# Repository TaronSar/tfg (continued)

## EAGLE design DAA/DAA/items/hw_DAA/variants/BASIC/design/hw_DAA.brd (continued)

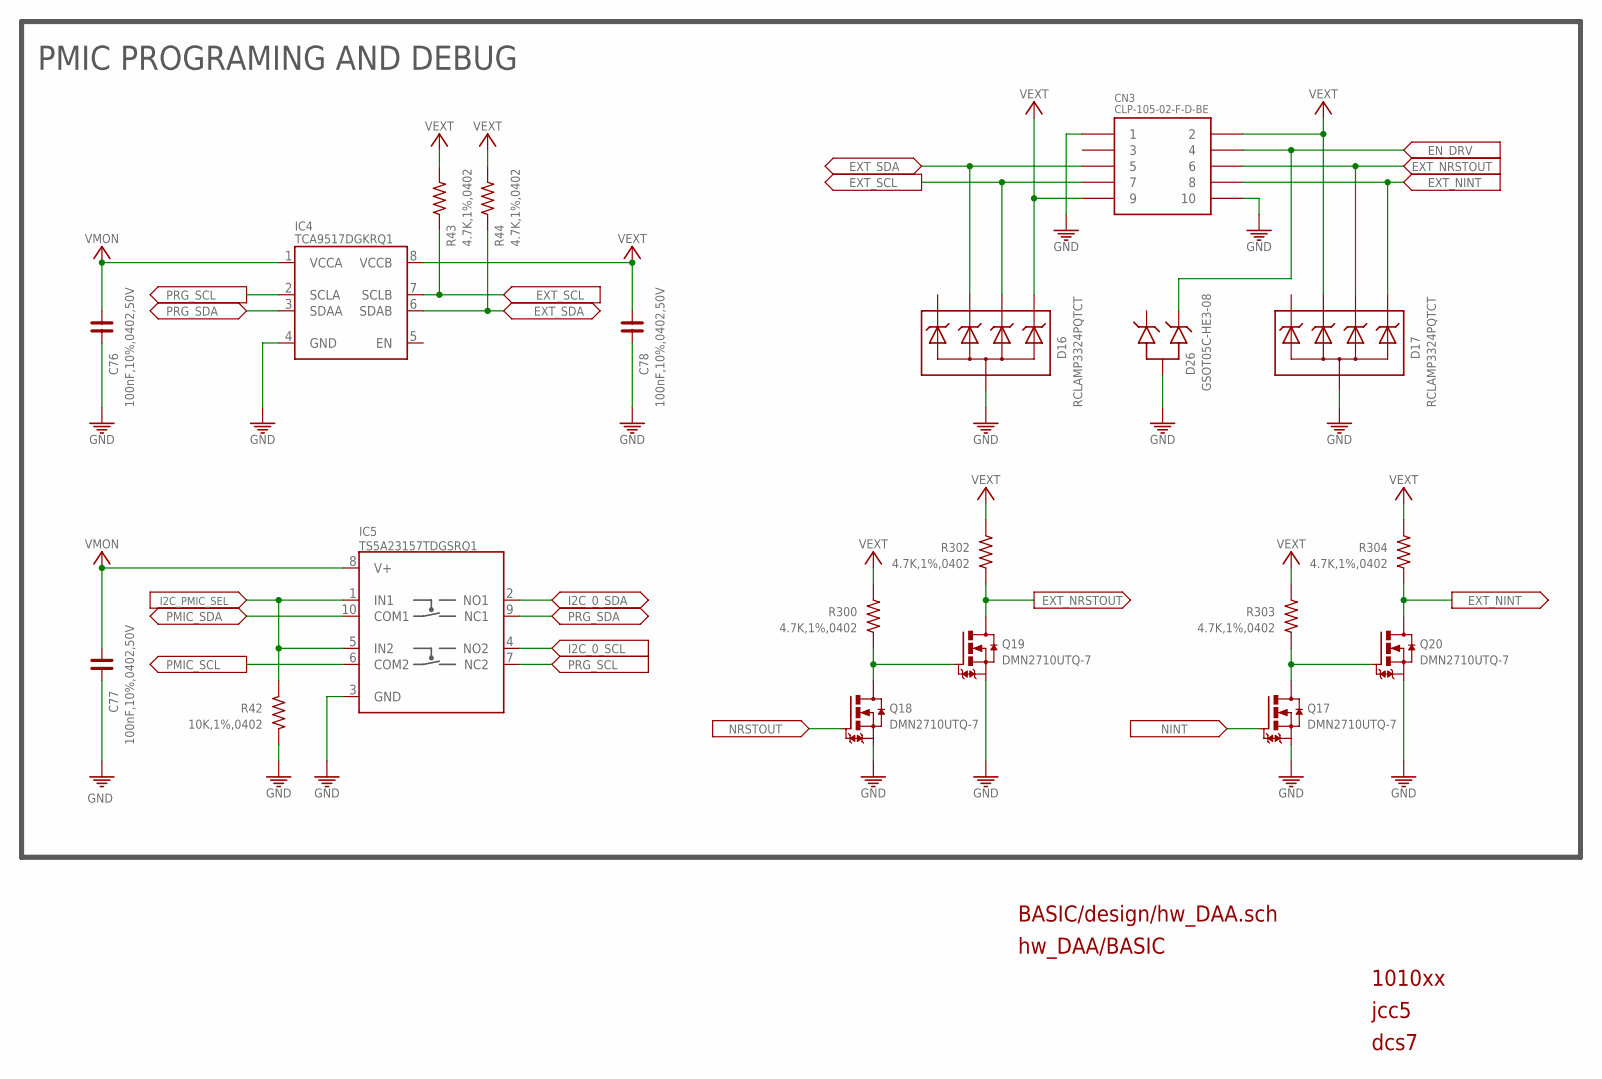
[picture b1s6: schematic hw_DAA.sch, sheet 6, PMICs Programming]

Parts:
C76, C77, C78: 100nF,10%,0402,50V; C0402
CN3: CLP-105-02-F-D-BE; CLP-105-02-X-D-BE
D16, D17: RCLAMP3324PQTCT; USON-10
D26: GSOT05C-HE3-08; SOT-23-3
IC4: TCA9517DGKRQ1; VSSOP-8(TEXAS)
IC5: TS5A23157TDGSRQ1; VSSOP-10
Q17, Q18, Q19, Q20: DMN2710UTQ-7; SOT-523
R42: 10K,1%,0402; R0402
R43, R44, R300, R302, R303, R304: 4.7K,1%,0402; R0402

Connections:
EN_DRV: CN3.4, D26.2; also elsewhere on the board
EXT_NINT: CN3.8, D17.5 (4), D17.6 (4), Q20.3 (D), R304.2
EXT_NRSTOUT: CN3.6, D17.4 (3), D17.7 (3), Q19.3 (D), R302.2
EXT_SCL: CN3.7, D16.4 (3), D16.7 (3), IC4.7 (SCLB), R43.2
EXT_SDA: CN3.5, D16.2, D16.9 (2), IC4.6 (SDAB), R44.2
GND: C76.2, C77.2, C78.2, CN3.1, CN3.10, D16.3 (5), D16.8 (5), D16.38 (5), D17.3 (5), D17.8 (5), D17.38 (5), D26.3, IC4.4 (GND), IC5.3 (GND), Q17.2 (S), Q18.2 (S), Q19.2 (S), Q20.2 (S), R42.1; also elsewhere on the board
I2C_0_SCL: IC5.4 (NO2); also elsewhere on the board
I2C_0_SDA: IC5.2 (NO1); also elsewhere on the board
I2C_PMIC_SEL: IC5.1 (IN1), IC5.5 (IN2), R42.2; also elsewhere on the board
unnamed: Q17.3 (D), Q20.1 (G), R303.2
unnamed: Q18.3 (D), Q19.1 (G), R300.2
NINT: Q17.1 (G); also elsewhere on the board
NRSTOUT: Q18.1 (G); also elsewhere on the board
PMIC_SCL: IC5.6 (COM2); also elsewhere on the board
PMIC_SDA: IC5.10 (COM1); also elsewhere on the board
PRG_SCL: IC4.2 (SCLA), IC5.7 (NC2)
PRG_SDA: IC4.3 (SDAA), IC5.9 (NC1)
VEXT: C78.1, CN3.2, CN3.9, D16.5 (4), D16.6 (4), D17.2, D17.9 (2), IC4.8 (VCCB), R43.1, R44.1, R300.1, R302.1, R303.1, R304.1
VMON: C76.1, C77.1, IC4.1 (VCCA), IC5.8 (V+); also elsewhere on the board

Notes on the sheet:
1010xx
jcc5
dcs7
PMIC PROGRAMING AND DEBUG
BASIC/design/hw_DAA.sch
hw_DAA/BASIC

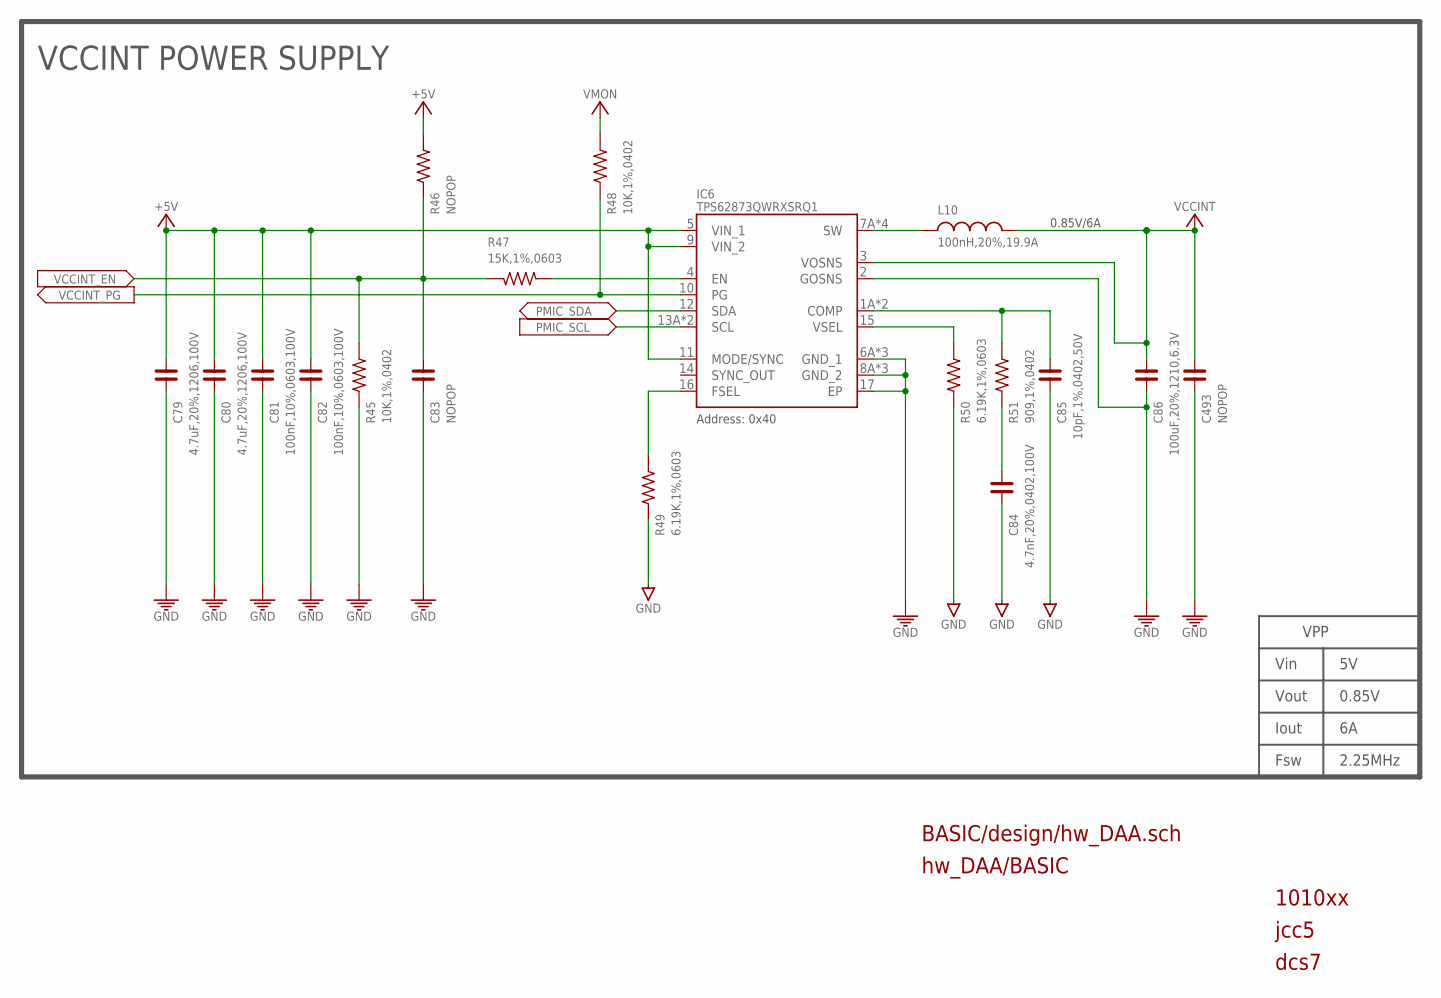
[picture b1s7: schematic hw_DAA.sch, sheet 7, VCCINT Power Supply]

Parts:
C79, C80: 4.7uF,20%,1206,100V; C1206
C81, C82: 100nF,10%,0603,100V; C0603
C83: NOPOP; C0402
C84: 4.7nF,20%,0402,100V; C0402
C85: 10pF,1%,0402,50V; C0402
C86: 100uF,20%,1210,6.3V; C1210
C493: NOPOP; C1210
IC6: TPS62873QWRXSRQ1; VQFN-16_RXS
L10: 100nH,20%,19.9A; XAL4020
R45, R48: 10K,1%,0402; R0402
R46: NOPOP; R0402
R47: 15K,1%,0603; R0603
R49, R50: 6.19K,1%,0603; R0603
R51: 909,1%,0402; R0402

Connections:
+5V: C79.1, C80.1, C81.1, C82.1, IC6.5 (VIN_1), IC6.9 (VIN_2), IC6.11 (MODE/SYNC), R46.2; also elsewhere on the board
GND: C79.2, C80.2, C81.2, C82.2, C83.2, C84.2, C85.2, C86.2, C493.2, IC6.2 (GOSNS), IC6.6A (GND_1), IC6.6B (GND_1), IC6.6C (GND_1), IC6.8A (GND_2), IC6.8B (GND_2), IC6.8C (GND_2), IC6.17 (EP), R45.1, R49.1, R50.1; also elsewhere on the board
unnamed: C85.1, IC6.1A (COMP), IC6.1B (COMP), R51.2
unnamed: C84.1, R51.1
unnamed: IC6.15 (VSEL), R50.2
unnamed: IC6.16 (FSEL), R49.2
unnamed: IC6.7A (SW), IC6.7B (SW), IC6.7C (SW), IC6.7D (SW), L10.1
unnamed: IC6.4 (EN), R47.2
PMIC_SCL: IC6.13A (SCL), IC6.13B (SCL); also elsewhere on the board
PMIC_SDA: IC6.12 (SDA); also elsewhere on the board
VCCINT: C86.1, C493.1, IC6.3 (VOSNS), L10.2; also elsewhere on the board
VCCINT_EN: C83.1, R45.2, R46.1, R47.1; also elsewhere on the board
VCCINT_PG: IC6.10 (PG), R48.1; also elsewhere on the board
VMON: R48.2; also elsewhere on the board

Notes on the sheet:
1010xx
jcc5
dcs7
0.85V/6A
Vout
Iout
Fsw
0.85V
Vin
VPP
2.25MHz
VCCINT POWER SUPPLY
Address: 0x40
BASIC/design/hw_DAA.sch
hw_DAA/BASIC

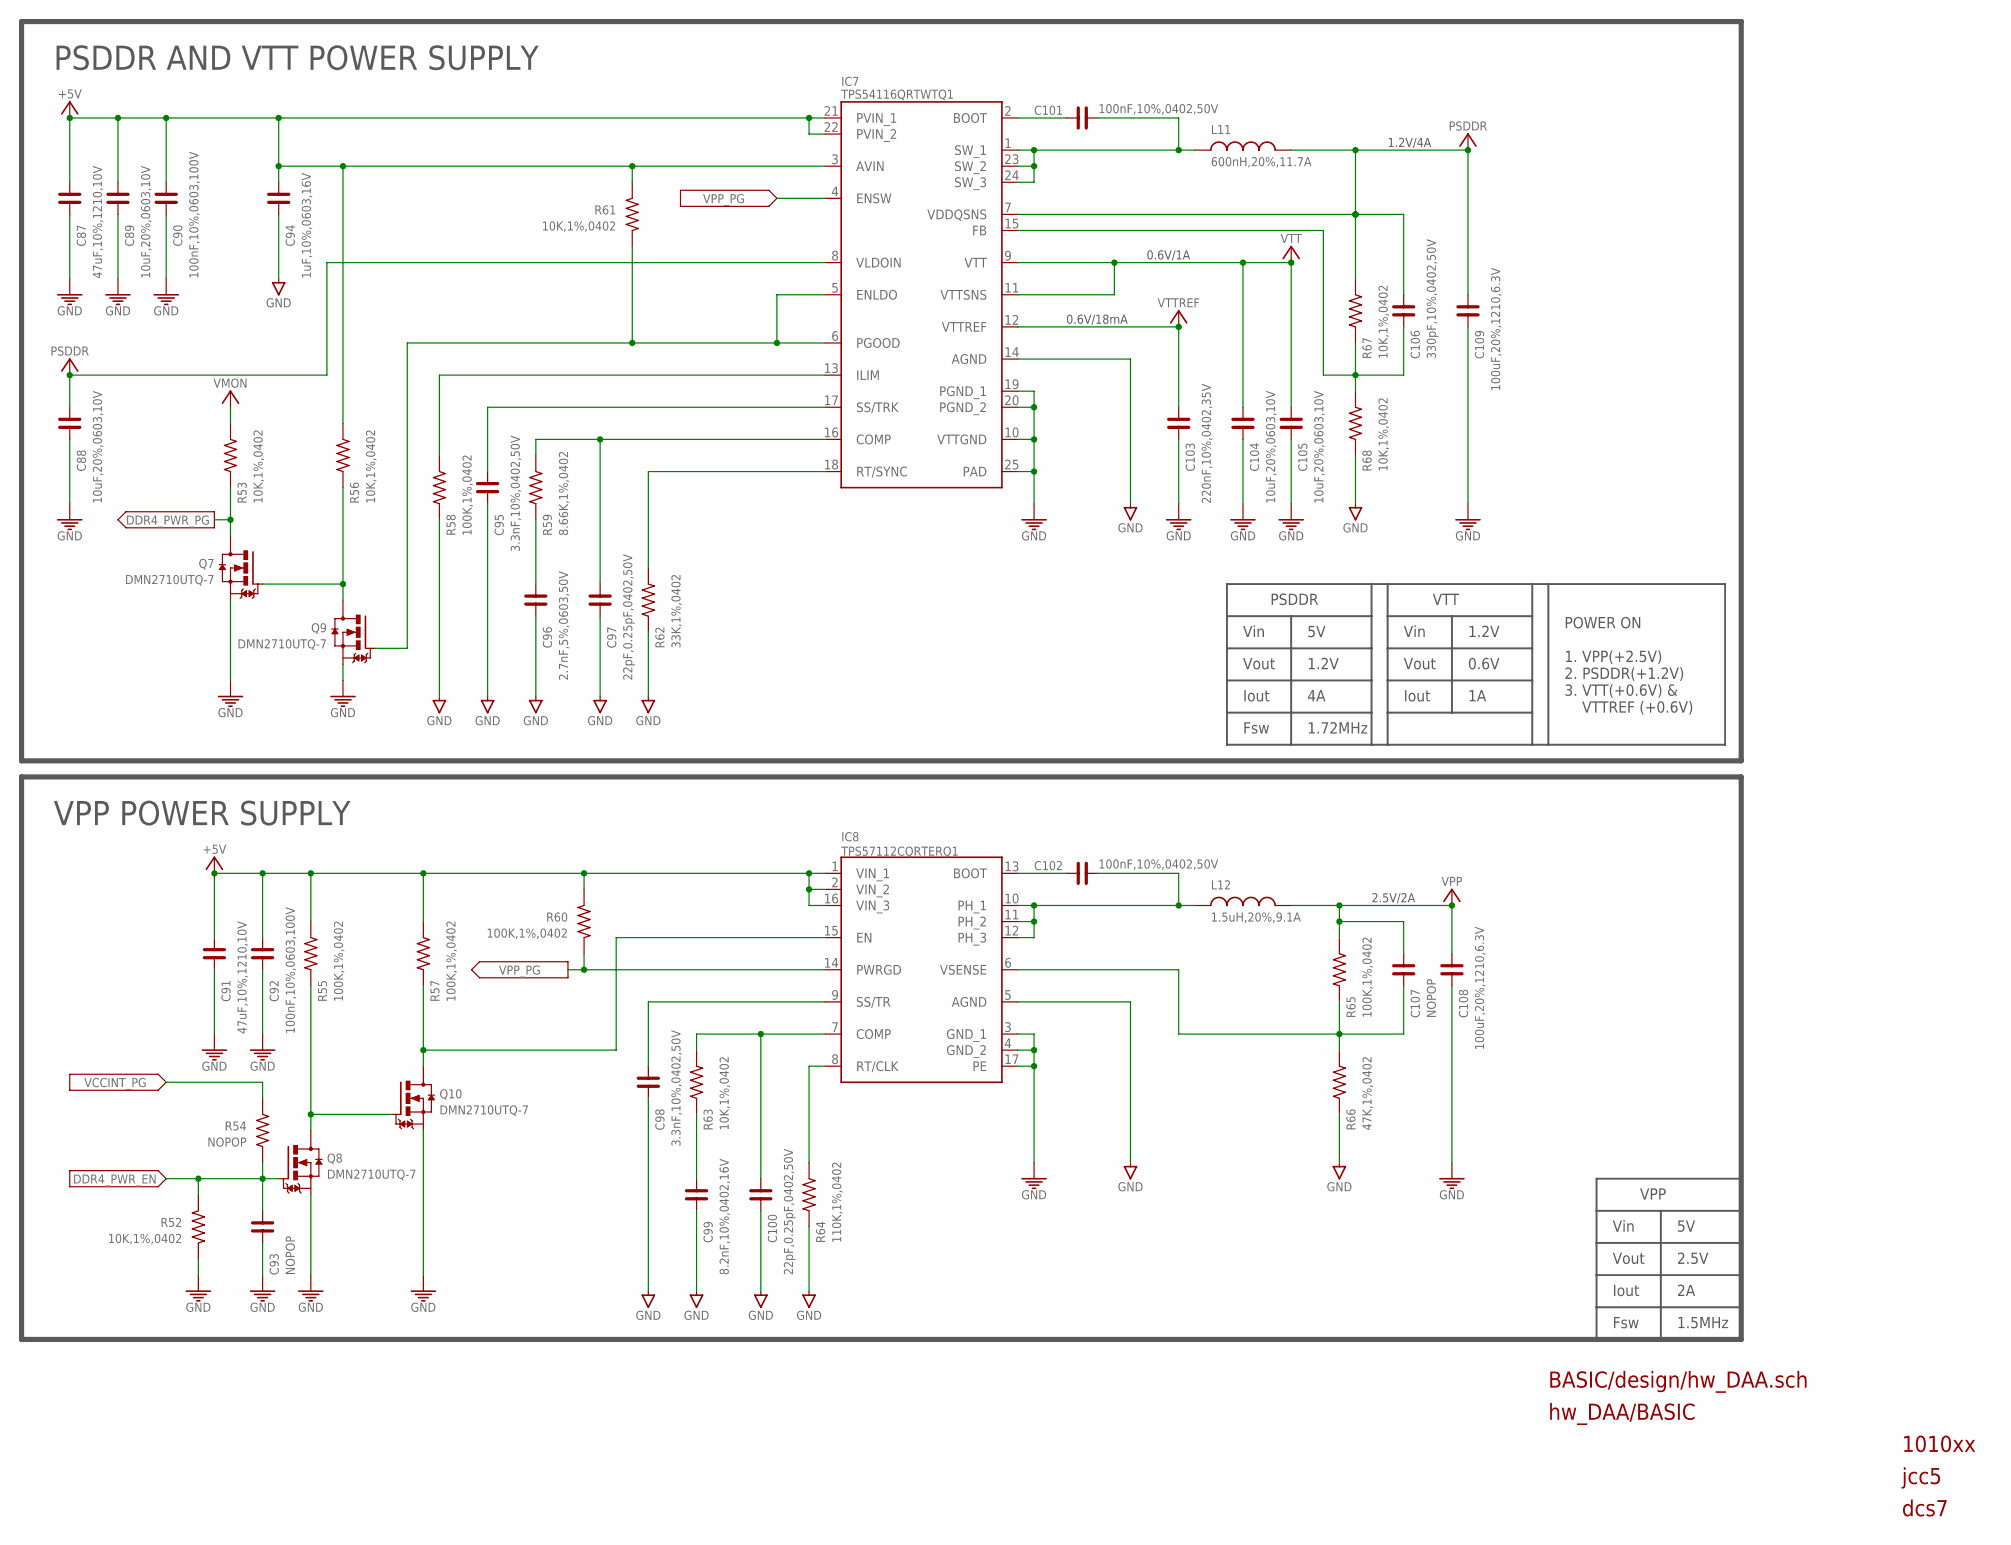
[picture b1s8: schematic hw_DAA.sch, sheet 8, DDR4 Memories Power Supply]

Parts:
C87, C91: 47uF,10%,1210,10V; C1210
C88, C89, C104, C105: 10uF,20%,0603,10V; C0603
C90, C92: 100nF,10%,0603,100V; C0603
C93, C107: NOPOP; C0402
C94: 1uF,10%,0603,16V; C0603
C95, C98: 3.3nF,10%,0402,50V; C0402
C96: 2.7nF,5%,0603,50V; C0603
C97, C100: 22pF,0.25pF,0402,50V; C0402
C99: 8.2nF,10%,0402,16V; C0402
C101, C102: 100nF,10%,0402,50V; C0402
C103: 220nF,10%,0402,35V; C0402
C106: 330pF,10%,0402,50V; C0402
C108, C109: 100uF,20%,1210,6.3V; C1210
IC7: TPS54116QRTWTQ1; WQFN-24
IC8: TPS57112CQRTERQ1; WQFN-16
L11: 600nH,20%,11.7A; XAL4020
L12: 1.5uH,20%,9.1A; XAL4020
Q7, Q8, Q9, Q10: DMN2710UTQ-7; SOT-523
R52, R53, R56, R61, R63, R67, R68: 10K,1%,0402; R0402
R54: NOPOP; R0402
R55, R57, R58, R60, R65: 100K,1%,0402; R0402
R59: 8.66K,1%,0402; R0402
R62: 33K,1%,0402; R0402
R64: 110K,1%,0402; R0402
R66: 47K,1%,0402; R0402

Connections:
+5V: C87.1, C89.1, C90.1, C91.1, C92.1, C94.1, IC7.3 (AVIN), IC7.21 (PVIN_1), IC7.22 (PVIN_2), IC8.1 (VIN_1), IC8.2 (VIN_2), IC8.16 (VIN_3), R55.2, R56.2, R57.2, R60.2, R61.2; also elsewhere on the board
DDR4_PWR_EN: C93.1, Q8.1 (G), R52.2, R54.1; also elsewhere on the board
DDR4_PWR_PG: Q7.3 (D), R53.1; also elsewhere on the board
EN_VPP: IC8.15 (EN), Q10.3 (D), R57.1
GND: C87.2, C88.2, C89.2, C90.2, C91.2, C92.2, C93.2, C94.2, C95.2, C96.2, C97.2, C98.2, C99.2, C100.2, C103.2, C104.2, C105.2, C108.2, C109.2, IC7.10 (VTTGND), IC7.14 (AGND), IC7.19 (PGND_1), IC7.20 (PGND_2), IC7.25 (PAD), IC8.3 (GND_1), IC8.4 (GND_2), IC8.5 (AGND), IC8.17 (PE), Q7.2 (S), Q8.2 (S), Q9.2 (S), Q10.2 (S), R52.1, R58.1, R62.1, R64.1, R66.1, R68.1; also elsewhere on the board
unnamed: C107.2, IC8.6 (VSENSE), R65.1, R66.2
unnamed: C98.1, IC8.9 (SS/TR)
unnamed: IC7.13 (ILIM), R58.2
unnamed: C95.1, IC7.17 (SS/TRK)
unnamed: C97.1, IC7.16 (COMP), R59.2
unnamed: C96.1, R59.1
unnamed: C100.1, IC8.7 (COMP), R63.2
unnamed: IC7.18 (RT/SYNC), R62.2
unnamed: C99.1, R63.1
unnamed: IC8.8 (RT/CLK), R64.2
unnamed: C106.2, IC7.15 (FB), R67.1, R68.2
unnamed: C102.2, IC8.13 (BOOT)
unnamed: C101.2, IC7.2 (BOOT)
unnamed: C101.1, IC7.1 (SW_1), IC7.23 (SW_2), IC7.24 (SW_3), L11.1
unnamed: C102.1, IC8.10 (PH_1), IC8.11 (PH_2), IC8.12 (PH_3), L12.1
unnamed: Q7.1 (G), Q9.3 (D), R56.1
unnamed: Q8.3 (D), Q10.1 (G), R55.1
PSDDR: C88.1, C106.1, C109.1, IC7.7 (VDDQSNS), IC7.8 (VLDOIN), L11.2, R67.2; also elsewhere on the board
PSDRR_PG: IC7.5 (ENLDO), IC7.6 (PGOOD), Q9.1 (G), R61.1
VCCINT_PG: R54.2; also elsewhere on the board
VMON: R53.2; also elsewhere on the board
VPP: C107.1, C108.1, L12.2, R65.2; also elsewhere on the board
VPP_PG: IC7.4 (ENSW), IC8.14 (PWRGD), R60.1
VTT: C104.1, C105.1, IC7.9 (VTT), IC7.11 (VTTSNS); also elsewhere on the board
VTTREF: C103.1, IC7.12 (VTTREF); also elsewhere on the board

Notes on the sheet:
1010xx
jcc5
dcs7
1.2V/4A
0.6V/1A
2.5V/2A
0.6V/18mA
PSDDR AND VTT POWER SUPPLY
VPP POWER SUPPLY
POWER ON 1. VPP(+2.5V) 2. PSDDR(+1.2V) 3. VTT(+0.6V) & VTTREF (+0.6V)
Vout
Iout
Fsw
1.2V
Vin
PSDDR
0.6V
VTT
1.72MHz
2.5V
VPP
1.5MHz
BASIC/design/hw_DAA.sch
hw_DAA/BASIC

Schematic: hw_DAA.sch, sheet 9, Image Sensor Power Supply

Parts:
C110, C111, C112: 10uF,10%,1206,35V; C1206
C113, C114, C119, C120, C121, C122: 10uF,10%,0805,16V; C0805
C115: 1uF,10%,0402,25V; C0402
C116, C118: 2.2uF,10%,0603,16V; C0603
C117: 100nF,10%,0402,50V; C0402
IC9: TPS65033000RGERQ1; VQFN-24
L13: 1.5uH,20%,2.3A; L201610
L14, L15: 1uH,20%,3.1A; L201610
R71, R73, R75: NOPOP; R0402
R72, R74: 0,5%,0402; R0402
R76: 1K,1%,0402; R0402

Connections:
!IMX_INT: IC9.22 (!INT), R72.1, R73.1
!IMX_RSTOUT: IC9.3 (!RSTOUT), R75.1; also elsewhere on the board
!TPS_INT: R72.2; also elsewhere on the board
+2V8: C118.1, IC9.24 (VLDO)
AVDD: C122.1, IC9.6 (FB_B1), L13.2; also elsewhere on the board
CM_SCL: IC9.1 (SCL); also elsewhere on the board
CM_SDA: IC9.2 (SDA); also elsewhere on the board
DVDD: C119.1, IC9.14 (FB_B3), L15.2; also elsewhere on the board
GND: C110.2, C111.2, C112.2, C113.2, C114.2, C115.2, C116.2, C118.2, C119.2, C120.2, C121.2, C122.2, IC9.5 (AGND), IC9.25 (PE), IC9.A11 (GND_1), IC9.A12 (GND_1), IC9.A21 (GND_2), IC9.A22 (GND_2), IC9.A31 (GND_3), IC9.A32 (GND_3), IC9.A41 (GND_4), IC9.A42 (GND_4); also elsewhere on the board
IMX_GPIO: IC9.19 (GPIO), R74.1
IMX_SEQ: IC9.10 (SEQ), R71.1, R76.2
IMX_VREG: C121.1, IC9.13 (VREG), R76.1
unnamed: IC9.20 (LX_B2), L14.1
unnamed: IC9.16 (LX_B3), L15.1
unnamed: C117.2, IC9.12 (BOOT)
unnamed: C117.1, IC9.11 (LX_B1), L13.1
unnamed: C114.1, IC9.4 (V1P8_INT)
OVDD: C115.1, C120.1, IC9.17 (VIO), IC9.18 (FB_B2), L14.2; also elsewhere on the board
POC: C110.1, C111.1, C112.1, C113.1, C116.1, IC9.7 (VSYS_S), IC9.8 (VSYS), IC9.9 (PVIN_B1), IC9.15 (PVIN_B3), IC9.21 (PVIN_B2), IC9.23 (PVINLDO); also elsewhere on the board
SER_GPIO0: R73.2; also elsewhere on the board
SER_PDB: R75.2; also elsewhere on the board
TPS_GPIO: R74.2; also elsewhere on the board
TPS_SEQ: R71.2; also elsewhere on the board

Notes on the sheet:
1010xx
jcc5
dcs7
3.3V/1.5A
1.8V/1.2A
1.2V/1.2A
IMAGE SENSOR POWER SUPPLY
1.8V
Address: 0x60
POWER ON 1. AVDD(+3.3V) 2. OVDD(+1.8V) 3. DVDD(+1.2V)
Vout
Iout
Fsw
3.3V
1.5A
2.3MHz
Vin
AVDD
1.2A
OVDD
1.2V
DVDD
BASIC/design/hw_DAA.sch
hw_DAA/BASIC

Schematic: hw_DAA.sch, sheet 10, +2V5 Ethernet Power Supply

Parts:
C123, C126: 2.2uF,10%,0603,16V; C0603
C124, C125: NOPOP; C0402
IC10: TPS74525PQWDRBRQ1; VSON-8
R77, R80, R81: NOPOP; R0402
R78, R79: 10K,1%,0402; R0402

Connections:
+2V5: C125.1, C126.1, IC10.1 (OUT), R80.2; also elsewhere on the board
+2V5_EN: C124.1, IC10.5 (EN), R77.1, R78.2; also elsewhere on the board
+2V5_PG: IC10.6 (PG), R79.1; also elsewhere on the board
+3V3: C123.1, IC10.8 (IN); also elsewhere on the board
DDR4_PWR_PG: R77.2; also elsewhere on the board
GND: C123.2, C124.2, C126.2, IC10.4 (GND), IC10.9 (EP), R78.1, R81.1; also elsewhere on the board
unnamed: C125.2, IC10.3 (NC_2/FB), R80.1, R81.2
VMON: R79.2; also elsewhere on the board

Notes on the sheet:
1010xx
jcc5
dcs7
+2V5 ETHERNET POWER SUPPLY
BASIC/design/hw_DAA.sch
hw_DAA/BASIC

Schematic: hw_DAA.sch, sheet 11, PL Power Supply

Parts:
C127, C140, C152, C155, C156, C158, C159: 47uF,20%,0603,4V; C0603
C128, C141, C142, C143, C145, C146, C147, C148, C151, C153, C154, C157: 10uF,20%,0402,4V; C0402
C129, C160: 330uF,20%,1210,2.5V; C1210
C130, C131, C132, C133, C136: 100uF,20%,0805,4V; C0805
C134: 470nF,10%,0402,16V; C0402
C135, C138, C139, C144, C149, C150: 4.7uF,20%,0402,10V; C0402
C137: 100nF,10%,0402,50V; C0402
FB4: BLM15PX121SH1D; L0402
IC11: XCZU15EG-2FFVB1156I; FFVB1156_NSMD
R82, R83: 100,1%,0402; R0402
R84, R85, R86, R87: 1K,1%,0402; R0402

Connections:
GND: C127.1, C128.1, C129.1, C130.1, C131.1, C132.1, C133.1, C135.1, C136.1, C138.1, C139.1, C140.1, C141.1, C142.1, C143.1, C144.1, C145.1, C146.1, C147.1, C148.1, C149.1, C150.1, C151.1, C152.1, C153.1, C154.1, C155.1, C156.1, C157.1, C158.1, C159.1, C160.1, R84.2, R85.2, R86.2, R87.2; also elsewhere on the board
GNDA: C134.1, C137.1; also elsewhere on the board
MGTAVCC: C135.2, C149.2, IC11.A10 (MGTAVCC_R_1), IC11.B8 (MGTAVCC_R_2), IC11.C6 (MGTAVCC_R_3), IC11.D7 (MGTAVCC_R_4), IC11.E5 (MGTAVCC_R_5), IC11.F28 (MGTAVCC_L_1), IC11.G6 (MGTAVCC_R_6), IC11.G29 (MGTAVCC_L_2), IC11.H27 (MGTAVCC_L_3), IC11.K8 (MGTAVCC_R_7), IC11.L29 (MGTAVCC_L_4), IC11.P28 (MGTAVCC_L_5), IC11.R29 (MGTAVCC_L_6); also elsewhere on the board
MGTAVTT: C138.2, C144.2, IC11.A5 (MGTAVTTRCAL_R), IC11.A30 (MGTAVTTRCAL_L), IC11.B3 (MGTAVTT_R_1), IC11.B31 (MGTAVTT_L_1), IC11.C29 (MGTAVTT_L_2), IC11.D4 (MGTAVTT_R_2), IC11.D32 (MGTAVTT_L_3), IC11.E30 (MGTAVTT_L_4), IC11.F3 (MGTAVTT_R_3), IC11.F31 (MGTAVTT_L_5), IC11.H4 (MGTAVTT_R_4), IC11.H32 (MGTAVTT_L_6), IC11.J5 (MGTAVTT_R_5), IC11.J30 (MGTAVTT_L_7), IC11.K3 (MGTAVTT_R_6), IC11.K31 (MGTAVTT_L_8), IC11.L6 (MGTAVTT_R_7), IC11.M4 (MGTAVTT_R_8), IC11.M32 (MGTAVTT_L_9), IC11.N5 (MGTAVTT_R_9), IC11.N30 (MGTAVTT_L_10), IC11.P3 (MGTAVTT_R_10), IC11.P31 (MGTAVTT_L_11), R82.2, R83.1; also elsewhere on the board
MGTRREF_L: IC11.A29 (MGTRREF_L), R82.1
MGTRREF_R: IC11.A6 (MGTRREF_R), R83.2
PSAVTT: C139.2, C150.2, IC11.F8 (MGTVCCAUX_R_1), IC11.H7 (MGTVCCAUX_R_2), IC11.K28 (MGTVCCAUX_L_1), IC11.M27 (MGTVCCAUX_L_2); also elsewhere on the board
VCCADC: C134.2, C137.2, FB4.1, IC11.T18 (VCCADC)
VCCAUX: C127.2, C128.2, C142.2, C143.2, C145.2, C146.2, C147.2, C148.2, C151.2, C152.2, C154.2, C156.2, C158.2, C160.2, FB4.2, IC11.AA9 (VCCO_66_3), IC11.AD8 (VCCO_65_1), IC11.AF9 (VCCO_65_2), IC11.AF14 (VCCO_44_1), IC11.AG7 (VCCO_65_3), IC11.AJ8 (VCCO_64_1), IC11.AJ13 (VCCO_44_2), IC11.AK11 (VCCO_64_3), IC11.AL9 (VCCO_64_2), IC11.E16 (VCCO_49_1), IC11.E21 (VCCO_47_1), IC11.F14 (VCCO_49_2), IC11.G12 (VCCO_50_1), IC11.G17 (VCCO_48_1), IC11.H20 (VCCO_47_2), IC11.J13 (VCCO_50_2), IC11.J18 (VCCO_48_2), IC11.T14 (VCCAUX_1), IC11.U13 (VCCAUX_HDIO), IC11.U14 (VCCAUX_2), IC11.V13 (VCCAUX_HPIO_1), IC11.V14 (VCCAUX_HPIO_2), IC11.W8 (VCCO_66_1), IC11.Y11 (VCCO_66_2); also elsewhere on the board
VCCINT: C129.2, C130.2, C131.2, C132.2, C133.2, C136.2, C140.2, C141.2, C153.2, C155.2, IC11.AA13 (VCCINT_IO_2), IC11.AA15 (VCCINT_25), IC11.AA17 (VCCINT_26), IC11.AA19 (VCCINT_27), IC11.AB13 (VCCINT_IO_3), IC11.AB14 (VCCBRAM_3), IC11.AB16 (VCCINT_28), IC11.AB18 (VCCINT_29), IC11.AB20 (VCCINT_30), IC11.AC13 (VCCINT_IO_4), IC11.AC14 (VCCBRAM_4), IC11.AC15 (VCCINT_31), IC11.AC17 (VCCINT_32), IC11.AC19 (VCCINT_33), IC11.M16 (VCCINT_1), IC11.M18 (VCCINT_2), IC11.M20 (VCCINT_3), IC11.N15 (VCCINT_4), IC11.N17 (VCCINT_5), IC11.N19 (VCCINT_6), IC11.P14 (VCCINT_7), IC11.P16 (VCCINT_8), IC11.P18 (VCCINT_9), IC11.P20 (VCCINT_10), IC11.R15 (VCCINT_11), IC11.R17 (VCCINT_12), IC11.R19 (VCCINT_13), IC11.T16 (VCCINT_14), IC11.T20 (VCCINT_15), IC11.U15 (VCCINT_16), IC11.U19 (VCCINT_17), IC11.V16 (VCCINT_18), IC11.V20 (VCCINT_19), IC11.W14 (VCCBRAM_1), IC11.W15 (VCCINT_20), IC11.W19 (VCCINT_21), IC11.Y13 (VCCINT_IO_1), IC11.Y14 (VCCBRAM_2), IC11.Y16 (VCCINT_22), IC11.Y18 (VCCINT_23), IC11.Y20 (VCCINT_24); also elsewhere on the board
VCC_3V3: C157.2, C159.2, IC11.P8 (VCCO_67_1), IC11.T9 (VCCO_67_2), IC11.U7 (VCCO_67_3); also elsewhere on the board
VREF_64: IC11.AJ11 (VREF_64), R87.1
VREF_65: IC11.AD11 (VREF_65), R86.1
VREF_66: IC11.AD12 (VREF_66), R85.1
VREF_67: IC11.N14 (VREF_67), R84.1

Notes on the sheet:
1010xx
jcc5
dcs7
POWER ON 1. VCCINT(+0.85V) 2. VCCAUX(+1.8V) 3. MGTAVCC(+0.9V) 4. MGTAVTT(+1.2V) 5. PSAVTT(+1.8V)
0.85V
1.2V
0.9V
1.8V
FPGA PROGRAMMABLE LOGIC POWER SUPPLY
120Ohm
BASIC/design/hw_DAA.sch
hw_DAA/BASIC

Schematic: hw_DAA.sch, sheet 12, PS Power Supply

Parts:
C161, C164, C167, C168, C172, C179, C182, C183, C184, C186, C188, C189, C190: 100uF,20%,0805,4V; C0805
C162, C165, C166, C169, C170, C174, C176, C177, C178, C180, C181, C185, C187: 10uF,20%,0402,4V; C0402
C163: 47uF,20%,0603,4V; C0603
C171: 470nF,10%,0402,16V; C0402
C173: 100nF,10%,0402,50V; C0402
C175: NOPOP; C0402
FB5, FB6: BLM15PX121SH1D; L0402
IC11: XCZU15EG-2FFVB1156I; FFVB1156_NSMD
R88: 0,5%,0402; R0402
R89: 499,1%,0402; R0402

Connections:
GND: C161.1, C162.1, C163.1, C164.1, C165.1, C166.1, C167.1, C168.1, C169.1, C170.1, C172.1, C174.1, C175.1, C176.1, C177.1, C178.1, C179.1, C180.1, C181.1, C182.1, C183.1, C184.1, C185.1, C186.1, C187.1, C188.1, C189.1, C190.1, R88.1, R89.2; also elsewhere on the board
GNDA: C171.1, C173.1; also elsewhere on the board
MGTAVTT: C168.2, C170.2, IC11.W22 (VCC_PSPLL_1), IC11.W24 (VCC_PSPLL_2), IC11.W25 (VCC_PSPLL_3); also elsewhere on the board
PSAVCC: C178.2, IC11.AA29 (PS_MGTRAVCC_4), IC11.V28 (PS_MGTRAVCC_1), IC11.W30 (PS_MGTRAVCC_2), IC11.Y27 (PS_MGTRAVCC_3); also elsewhere on the board
PSAVTT: C176.2, IC11.AB32 (PS_MGTRAVTT_3), IC11.V32 (PS_MGTRAVTT_1), IC11.Y31 (PS_MGTRAVTT_2); also elsewhere on the board
PSDDR: C181.2, C183.2, C184.2, IC11.AG27 (VCCO_PSDDR_504_1), IC11.AJ24 (VCCO_PSDDR_504_2), IC11.AJ28 (VCCO_PSDDR_504_3), IC11.AL24 (VCCO_PSDDR_504_4), IC11.AL29 (VCCO_PSDDR_504_5), IC11.AN25 (VCCO_PSDDR_504_6), IC11.AN30 (VCCO_PSDDR_504_7); also elsewhere on the board
PS_MGTRREF_505: IC11.AB28 (PS_MGTRREF_505), R89.1
VCCAUX: C161.2, C162.2, C180.2, C182.2, C185.2, C186.2, FB5.2, FB6.2, IC11.AA23 (VCC_PSAUX_3), IC11.AA25 (VCC_PSAUX_4), IC11.D23 (VCCO_PSIO2_502_1), IC11.F24 (VCCO_PSIO2_502_2), IC11.G22 (VCCO_PSIO2_502_3), IC11.L24 (VCCO_PSIO1_501_1), IC11.M22 (VCCO_PSIO1_501_2), IC11.Y22 (VCC_PSAUX_1), IC11.Y23 (VCC_PSAUX_2); also elsewhere on the board
VCCINT: C164.2, C166.2, C167.2, C169.2, C172.2, C174.2, IC11.AA21 (VCC_PSINTLP_1), IC11.AB21 (VCC_PSINTLP_2), IC11.AB23 (VCC_PSINTLP_3), IC11.AC21 (VCC_PSINTLP_4), IC11.AC22 (VCC_PSINTLP_5), IC11.AC23 (VCC_PSINTLP_6), IC11.AC24 (VCC_PSINTFP_1), IC11.AD21 (VCC_PSINTFP_2), IC11.AD22 (VCC_PSINTFP_3), IC11.AD24 (VCC_PSINTFP_DDR_1), IC11.AD25 (VCC_PSINTFP_4), IC11.AD26 (VCC_PSINTFP_5), IC11.AE22 (VCC_PSINTFP_6), IC11.AE23 (VCC_PSINTFP_7), IC11.AE24 (VCC_PSINTFP_DDR_2), IC11.AE25 (VCC_PSINTFP_DDR_3); also elsewhere on the board
VCC_3V3: C177.2, C179.2, C187.2, C188.2, C189.2, C190.2, IC11.AE16 (VCCO_PSIO0_500_1), IC11.AG17 (VCCO_PSIO0_500_2), IC11.AK16 (VCCO_PSIO0_500_3), IC11.T24 (VCCO_PSIO3_503_1), IC11.U22 (VCCO_PSIO3_503_2); also elsewhere on the board
VCC_PSADC: C171.2, C173.2, FB6.1, IC11.AB25 (VCC_PSADC_1), IC11.AC26 (VCC_PSADC_2)
VCC_PSBATT: C175.2, IC11.AA22 (VCC_PSBATT), R88.2
VCC_PSDDR_PLL: C163.2, C165.2, FB5.1, IC11.Y24 (VCC_PSDDR_PLL_1), IC11.Y25 (VCC_PSDDR_PLL_2)

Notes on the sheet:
1010xx
jcc5
dcs7
1.8V
0.85V
1.2V
3.3V
FPGA PROCESSING SYSTEM POWER SUPPLY
POWER ON 1. VCCINT(+0.85V) 2. VCCAUX(+1.8V) 3. VCC_3V3 (+3.3V) 4. MGTAVCC(+0.9V) 5. MGTAVTT(+1.2V) 6. PSAVTT(+1.8V) 7. PSAVCC(+0.85V) 8. PSDDR(+1.2V)
120Ohm
BASIC/design/hw_DAA.sch
hw_DAA/BASIC

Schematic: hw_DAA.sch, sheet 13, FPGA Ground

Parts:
FB7: BLM15PX121SH1D; L0402
IC11: XCZU15EG-2FFVB1156I; FFVB1156_NSMD

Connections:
GND: FB7.1, IC11.A1 (GND_1), IC11.A2 (GND_2), IC11.A9 (GND_3), IC11.A11 (GND_4), IC11.A14 (GND_5), IC11.A19 (GND_6), IC11.A24 (GND_7), IC11.A28 (GND_8), IC11.A33 (GND_9), IC11.A34 (GND_10), IC11.AA4 (GND_189), IC11.AA14 (GND_190), IC11.AA16 (GND_191), IC11.AA18 (GND_192), IC11.AA20 (GND_193), IC11.AA24 (GND_194), IC11.AA26 (GND_195), IC11.AA30 (GND_196), IC11.AA33 (GND_197), IC11.AA34 (GND_198), IC11.AB2 (GND_199), IC11.AB7 (GND_200), IC11.AB12 (GND_201), IC11.AB15 (GND_202), IC11.AB17 (GND_203), IC11.AB19 (GND_204), IC11.AB22 (GND_205), IC11.AB26 (GND_206), IC11.AB27 (GND_207), IC11.AB31 (GND_208), IC11.AC5 (GND_209), IC11.AC10 (GND_210), IC11.AC16 (GND_211), IC11.AC18 (GND_212), IC11.AC20 (GND_213), IC11.AC27 (GND_214), IC11.AC28 (GND_215), IC11.AC29 (GND_216), IC11.AC30 (GND_217), IC11.AC31 (GND_218), IC11.AC32 (GND_219), IC11.AC33 (GND_220), IC11.AC34 (GND_221), IC11.AD3 (GND_222), IC11.AD13 (GND_223), IC11.AD23 (GND_224), IC11.AE6 (GND_225), IC11.AE11 (GND_226), IC11.AE21 (GND_227), IC11.AE26 (GND_228), IC11.AE31 (GND_229), IC11.AF4 (GND_230), IC11.AF19 (GND_231), IC11.AF24 (GND_232), IC11.AF29 (GND_233), IC11.AF34 (GND_234), IC11.AG2 (GND_235), IC11.AG12 (GND_236), IC11.AG22 (GND_237), IC11.AG32 (GND_238), IC11.AH5 (GND_239), IC11.AH10 (GND_240), IC11.AH15 (GND_241), IC11.AH20 (GND_242), IC11.AH25 (GND_243), IC11.AH30 (GND_244), IC11.AJ3 (GND_245), IC11.AJ18 (GND_246), IC11.AJ23 (GND_247), IC11.AJ33 (GND_248), IC11.AK6 (GND_249), IC11.AK21 (GND_250), IC11.AK26 (GND_251), IC11.AK31 (GND_252), IC11.AL4 (GND_253), IC11.AL14 (GND_254), IC11.AL19 (GND_255), IC11.AL34 (GND_256), IC11.AM2 (GND_257), IC11.AM7 (GND_258), IC11.AM12 (GND_259), IC11.AM17 (GND_260), IC11.AM22 (GND_261), IC11.AM27 (GND_262), IC11.AM32 (GND_263), IC11.AN5 (GND_264), IC11.AN10 (GND_265), IC11.AN15 (GND_266), IC11.AN20 (GND_267), IC11.AP13 (GND_268), IC11.AP23 (GND_269), IC11.AP28 (GND_270), IC11.AP34 (GND_271), IC11.B4 (GND_11), IC11.B7 (GND_12), IC11.B11 (GND_13), IC11.B17 (GND_14), IC11.B22 (GND_15), IC11.B28 (GND_16), IC11.B32 (GND_17), IC11.C1 (GND_18), IC11.C2 (GND_19), IC11.C5 (GND_20), IC11.C9 (GND_21), IC11.C10 (GND_22), IC11.C11 (GND_23), IC11.C15 (GND_24), IC11.C20 (GND_25), IC11.C25 (GND_26), IC11.C28 (GND_27), IC11.C30 (GND_28), IC11.C33 (GND_29), IC11.C34 (GND_30), IC11.D3 (GND_31), IC11.D8 (GND_32), IC11.D9 (GND_33), IC11.D13 (GND_34), IC11.D18 (GND_35), IC11.D26 (GND_36), IC11.D27 (GND_37), IC11.D28 (GND_38), IC11.D31 (GND_39), IC11.E1 (GND_40), IC11.E2 (GND_41), IC11.E6 (GND_42), IC11.E9 (GND_43), IC11.E11 (GND_44), IC11.E26 (GND_45), IC11.E29 (GND_46), IC11.E33 (GND_47), IC11.E34 (GND_48), IC11.F4 (GND_49), IC11.F7 (GND_50), IC11.F9 (GND_51), IC11.F19 (GND_52), IC11.F26 (GND_53), IC11.F27 (GND_54), IC11.F32 (GND_55), IC11.G1 (GND_56), IC11.G2 (GND_57), IC11.G5 (GND_58), IC11.G9 (GND_59), IC11.G26 (GND_60), IC11.G30 (GND_61), IC11.G33 (GND_62), IC11.G34 (GND_63), IC11.H3 (GND_64), IC11.H8 (GND_65), IC11.H9 (GND_66), IC11.H15 (GND_67), IC11.H26 (GND_68), IC11.H28 (GND_69), IC11.H31 (GND_70), IC11.J1 (GND_71), IC11.J2 (GND_72), IC11.J6 (GND_73), IC11.J9 (GND_74), IC11.J23 (GND_75), IC11.J26 (GND_76), IC11.J29 (GND_77), IC11.J33 (GND_78), IC11.J34 (GND_79), IC11.K4 (GND_80), IC11.K7 (GND_81), IC11.K9 (GND_82), IC11.K11 (GND_83), IC11.K21 (GND_84), IC11.K26 (GND_85), IC11.K27 (GND_86), IC11.K32 (GND_87), IC11.L1 (GND_88), IC11.L2 (GND_89), IC11.L5 (GND_90), IC11.L9 (GND_91), IC11.L14 (GND_92), IC11.L26 (GND_93), IC11.L30 (GND_94), IC11.L33 (GND_95), IC11.L34 (GND_96), IC11.M3 (GND_97), IC11.M7 (GND_98), IC11.M8 (GND_99), IC11.M9 (GND_100), IC11.M12 (GND_101), IC11.M17 (GND_102), IC11.M19 (GND_103), IC11.M26 (GND_104), IC11.M28 (GND_105), IC11.M31 (GND_106), IC11.N1 (GND_107), IC11.N2 (GND_108), IC11.N6 (GND_109), IC11.N7 (GND_110), IC11.N10 (GND_111), IC11.N16 (GND_112), IC11.N18 (GND_113), IC11.N20 (GND_114), IC11.N26 (GND_115), IC11.N29 (GND_116), IC11.N33 (GND_117), IC11.N34 (GND_118), IC11.P4 (GND_119), IC11.P7 (GND_120), IC11.P13 (GND_121), IC11.P15 (GND_122), IC11.P17 (GND_123), IC11.P19 (GND_124), IC11.P23 (GND_125), IC11.P26 (GND_126), IC11.P27 (GND_127), IC11.P32 (GND_128), IC11.R1 (GND_129), IC11.R2 (GND_130), IC11.R5 (GND_131), IC11.R6 (GND_132), IC11.R7 (GND_133), IC11.R11 (GND_134), IC11.R14 (GND_135), IC11.R16 (GND_136), IC11.R18 (GND_137), IC11.R20 (GND_138), IC11.R26 (GND_139), IC11.R30 (GND_140), IC11.R33 (GND_141), IC11.R34 (GND_142), IC11.T3 (GND_143), IC11.T4 (GND_144), IC11.T5 (GND_145), IC11.T15 (GND_146), IC11.T19 (GND_147), IC11.T26 (GND_148), IC11.T27 (GND_149), IC11.T28 (GND_150), IC11.T31 (GND_151), IC11.T32 (GND_152), IC11.U1 (GND_153), IC11.U2 (GND_154), IC11.U3 (GND_155), IC11.U12 (GND_156), IC11.U16 (GND_157), IC11.U20 (GND_158), IC11.U26 (GND_159), IC11.U29 (GND_160), IC11.U30 (GND_161), IC11.U33 (GND_162), IC11.U34 (GND_163), IC11.V5 (GND_164), IC11.V10 (GND_165), IC11.V15 (GND_166), IC11.V19 (GND_167), IC11.V25 (GND_168), IC11.V26 (GND_169), IC11.V27 (GND_170), IC11.V31 (GND_171), IC11.W3 (GND_172), IC11.W13 (GND_173), IC11.W16 (GND_174), IC11.W20 (GND_175), IC11.W23 (GND_176), IC11.W26 (GND_177), IC11.W29 (GND_178), IC11.W33 (GND_179), IC11.W34 (GND_180), IC11.Y6 (GND_181), IC11.Y15 (GND_182), IC11.Y17 (GND_183), IC11.Y19 (GND_184), IC11.Y21 (GND_185), IC11.Y26 (GND_186), IC11.Y28 (GND_188), IC11.Y32 (GND_187); also elsewhere on the board
GNDA: FB7.2, IC11.AB24 (GND_PSADC_1), IC11.AC25 (GND_PSADC_2), IC11.T17 (GNDADC); also elsewhere on the board

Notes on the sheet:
1010xx
jcc5
dcs7
FPGA GROUND
120Ohm
BASIC/design/hw_DAA.sch
hw_DAA/BASIC

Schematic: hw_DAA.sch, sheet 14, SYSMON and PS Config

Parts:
C191: 33pF,5%,0402,50V; C0402
C192, C193, C196: 100nF,10%,0402,50V; C0402
C194, C195: 22pF,0.25pF,0402,50V; C0402
CN4: CLP-106-02-F-D-BE; CLP-106-02-X-D-BE
CN5: CLP-105-02-F-D-BE; CLP-105-02-X-D-BE
D18, D20, D21, D22: RCLAMP3324PQTCT; USON-10
D19: BZT52C3V3-7-F; SOD123
IC11: XCZU15EG-2FFVB1156I; FFVB1156_NSMD
R90, R92, R94, R95, R99, R102, R104, R105, R107, R108, R110, R111, R112, R114, R116, R119: 4.7K,1%,0402; R0402
R91: 20,1%,0402; R0402
R93, R97, R103, R106, R109, R113, R115, R117, R118: NOPOP; R0402
R96, R121: 1K,1%,0402; R0402
R98: 0,5%,0402; R0402
R100, R101: 499,1%,0402; R0402
R120: 4.7M,1%,0402; R0402
Y2: SIT8008BI-11-33E-33.333333; 2.5X2
Y3: ECS-.327-12.5-34QCS-TR; 3.2X1.5

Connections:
+3V3_JTAG: CN4.1, CN4.12, D19.C, R98.1
DONE: CN5.7, D21.1, D21.10 (1), IC11.W21 (PS_DONE), R105.2
DX_O_N: IC11.W17 (DXN); also elsewhere on the board
DX_O_P: IC11.W18 (DXP); also elsewhere on the board
ERROR_OUT: CN5.5, D21.2, D21.9 (2), IC11.T21 (PS_ERROR_OUT), R101.2
ERROR_STAT: CN5.3, D21.4 (3), D21.7 (3), IC11.R21 (PS_ERROR_STATUS), R100.2
GND: C191.2, C192.2, C193.2, C194.2, C195.2, C196.2, CN4.2, CN4.11, CN5.2, CN5.9, D18.3 (5), D18.8 (5), D18.38 (5), D19.A, D20.3 (5), D20.8 (5), D20.38 (5), D21.3 (5), D21.8 (5), D21.38 (5), D22.3 (5), D22.8 (5), D22.38 (5), R94.1, R97.1, R100.1, R101.1, R104.1, R107.1, R110.1, R113.1, R115.1, R117.1, R119.1, Y2.2 (GND); also elsewhere on the board
GNDA: IC11.U17 (VREFN), IC11.U18 (VP), IC11.V17 (VN), IC11.V18 (VREFP); also elsewhere on the board
ID0: R103.1, R104.2; also elsewhere on the board
ID1: R106.1, R107.2; also elsewhere on the board
ID2: R109.1, R110.2; also elsewhere on the board
INIT_B: CN5.8, D22.2, D22.9 (2), IC11.V24 (PS_INIT_B), R102.2
JTCK: CN4.9, D18.1, D18.10 (1), IC11.R25 (PS_JTAG_TCK), R90.1, R91.2
JTDI: CN4.7, D18.2, D18.9 (2), IC11.U25 (PS_JTAG_TDI), R92.1
JTDO: CN4.5, D18.4 (3), D18.7 (3), IC11.T25 (PS_JTAG_TDO), R95.1
JTMS: CN4.4, D20.5 (4), D20.6 (4), IC11.R24 (PS_JTAG_TMS), R99.1
MODE0: IC11.T22 (PS_MODE0), R118.1, R119.2
MODE1: IC11.R22 (PS_MODE1), R116.1, R117.2
MODE2: IC11.T23 (PS_MODE2), R114.1, R115.2
MODE3: IC11.R23 (PS_MODE3), R112.1, R113.2
unnamed: R121.1, Y2.1 (EOH)
unnamed: C191.1, R91.1
PADI: C195.1, IC11.V21 (PS_PADI), R120.2, Y3.2 (X2)
PADO: C194.1, IC11.V22 (PS_PADO), R120.1, Y3.1 (X1)
POR_B: C192.1, CN4.8, D20.2, D20.9 (2), IC11.V23 (PS_POR_B); also elsewhere on the board
POR_OVERRIDE: IC11.AD14 (POR_OVERRIDE), R93.1, R94.2
PROG_B: CN5.6, D22.4 (3), D22.7 (3), IC11.U21 (PS_PROG_B), R108.1
PUDC_B: IC11.AD15 (PUDC_B), R96.1, R97.2
REF_CLK: IC11.U24 (PS_REF_CLK), Y2.3 (OUT)
SRST_B: C193.1, CN4.6, D20.4 (3), D20.7 (3), IC11.U23 (PS_SRST_B), R111.1
UART_2_RX: CN4.3, D18.5 (4), D18.6 (4); also elsewhere on the board
UART_2_TX: CN4.10, D20.1, D20.10 (1); also elsewhere on the board
VCCAUX: R96.2; also elsewhere on the board
VCCINT: R93.2; also elsewhere on the board
VCC_3V3: C196.1, CN5.1, CN5.10, D21.5 (4), D21.6 (4), D22.1, D22.10 (1), R90.2, R92.2, R95.2, R98.2, R99.2, R102.1, R103.2, R105.1, R106.2, R108.2, R109.2, R111.2, R112.2, R114.2, R116.2, R118.2, R121.2, Y2.4 (VCC); also elsewhere on the board

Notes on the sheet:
1010xx
jcc5
dcs7
33.333MHz
32.768kHz
SYSTEM MONITOR
BANK 503 JTAG, BOOT, RESETS CLOCKS AND STATUS
PROGRAMING CONNECTOR
ID RESISTORS
AUX DEBUGGIN CONNECTOR
BASIC/design/hw_DAA.sch
hw_DAA/BASIC

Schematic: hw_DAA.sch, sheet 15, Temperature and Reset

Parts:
C197, C199: 100nF,10%,0402,50V; C0402
C198: 100pF,5%,0402,50V; C0402
C200: NOPOP; C0402
IC12: SN74LVC1G08QDCKRQ1; DCK5
IC13: TMP451HQDQFRQ1; WSON-8
Q11, Q12: DMN2710UTQ-7; SOT-523
R122, R123: 56,1%,0402; R0402
R124: NOPOP; R0402
R125: 0,5%,0402; R0402
R126: 10K,1%,0402; R0402
R127, R128, R129, R130, R131, R354, R355: 4.7K,1%,0402; R0402

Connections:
!TEMP_ALERT: IC13.6 (!ALERT/THERM2), R128.1; also elsewhere on the board
!TEMP_THERM: IC13.4 (!THERM), R125.1, R129.1
DX_I_N: C198.2, IC13.3 (D-), R123.2
DX_I_P: C198.1, IC13.2 (D+), R122.2
DX_O_N: R123.1; also elsewhere on the board
DX_O_P: R122.1; also elsewhere on the board
GND: C197.2, C199.2, C200.2, IC12.3 (GND), IC13.5 (GND), Q11.2 (S), Q12.2 (S); also elsewhere on the board
I2C_1_SCL: IC13.8 (SCL), R354.1; also elsewhere on the board
I2C_1_SDA: IC13.7 (SDA), R355.1; also elsewhere on the board
unnamed: IC12.2 (B), R125.2
unnamed: Q11.3 (D), Q12.1 (G), R130.1
unnamed: IC12.4 (Y), Q11.1 (G), R124.2, R127.1
NRSTOUT: IC12.1 (A), R124.1, R126.2; also elsewhere on the board
POR_B: C200.1, Q12.3 (D), R131.2; also elsewhere on the board
VCCAUX: C197.1, C199.1, IC12.5 (VCC), IC13.1 (V+), R126.1, R127.2, R128.2, R129.2, R130.2, R354.2, R355.2; also elsewhere on the board
VCC_3V3: R131.1; also elsewhere on the board

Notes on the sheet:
1010xx
jcc5
dcs7
Address: 0x31
FPGA/LOCAL TEMPERATURE SENSOR
1.8V
RESET LOGIC
BASIC/design/hw_DAA.sch
hw_DAA/BASIC

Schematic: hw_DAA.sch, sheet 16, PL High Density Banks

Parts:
IC11: XCZU15EG-2FFVB1156I; FFVB1156_NSMD

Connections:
ETH_CLKO: IC11.A21 (IO_L11P_AD1P_47); also elsewhere on the board
SDIO_1_CLKFB: IC11.L20 (IO_L1P_AD11P_47); also elsewhere on the board

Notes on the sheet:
1010xx
jcc5
dcs7
PL HIGH DENSITY BANKS
BASIC/design/hw_DAA.sch
hw_DAA/BASIC
